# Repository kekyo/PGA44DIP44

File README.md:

# PGA44 to DIP44 socket PCB project

## What is this?

* This is very simple electric circuit diagram on EAGLE CAD.
* This is my first trial for learn how to use EAGLE CAD.
* I made for prototyping CPLD device (Xilinx XC95 series) on the breadboards.

## Artworks

* Xilinx XC9536/XC9572 version

* Side-by-side pure converter version

## How to use

### Xilinx XC9536/XC9572 version

TODO: More improving...

* You have to solder PGA44-PLCC44 socket and DIP22 x 2 headers.
* If your usage is side by side mapped pin conversion, you have to no additional works.
* If your usage is Xilinx XC95 series, add jumper pin header to head of board and solder x2 path-capacitors (ex: 0.1uF) onto SMD jumpers bottom of center board.
  * SMD jumpers shorts circuit between 21-41(VCCINT), 23-10-31(GND).
  * If jumper pin header closed, it shorts circuit between VCCINT and VCCIO. It means commonly voltage usage.

TODO: Example solder photos.

### Side-by-side pure converter version

* You have to solder PGA44-PLCC44 socket and DIP22 x 2 headers.
* Done!

TODO: Example solder photos.

## LICENSE

* [Under CC BY-NC-SA 4.0](https://creativecommons.org/licenses/by-nc-sa/4.0/)

## History

* 1.1
  * Fatal misassignement fixed for PGA44.
  * Split simple side-by-side pure converter version (see also pure-converter branch).
* 1.0
  * First public release.

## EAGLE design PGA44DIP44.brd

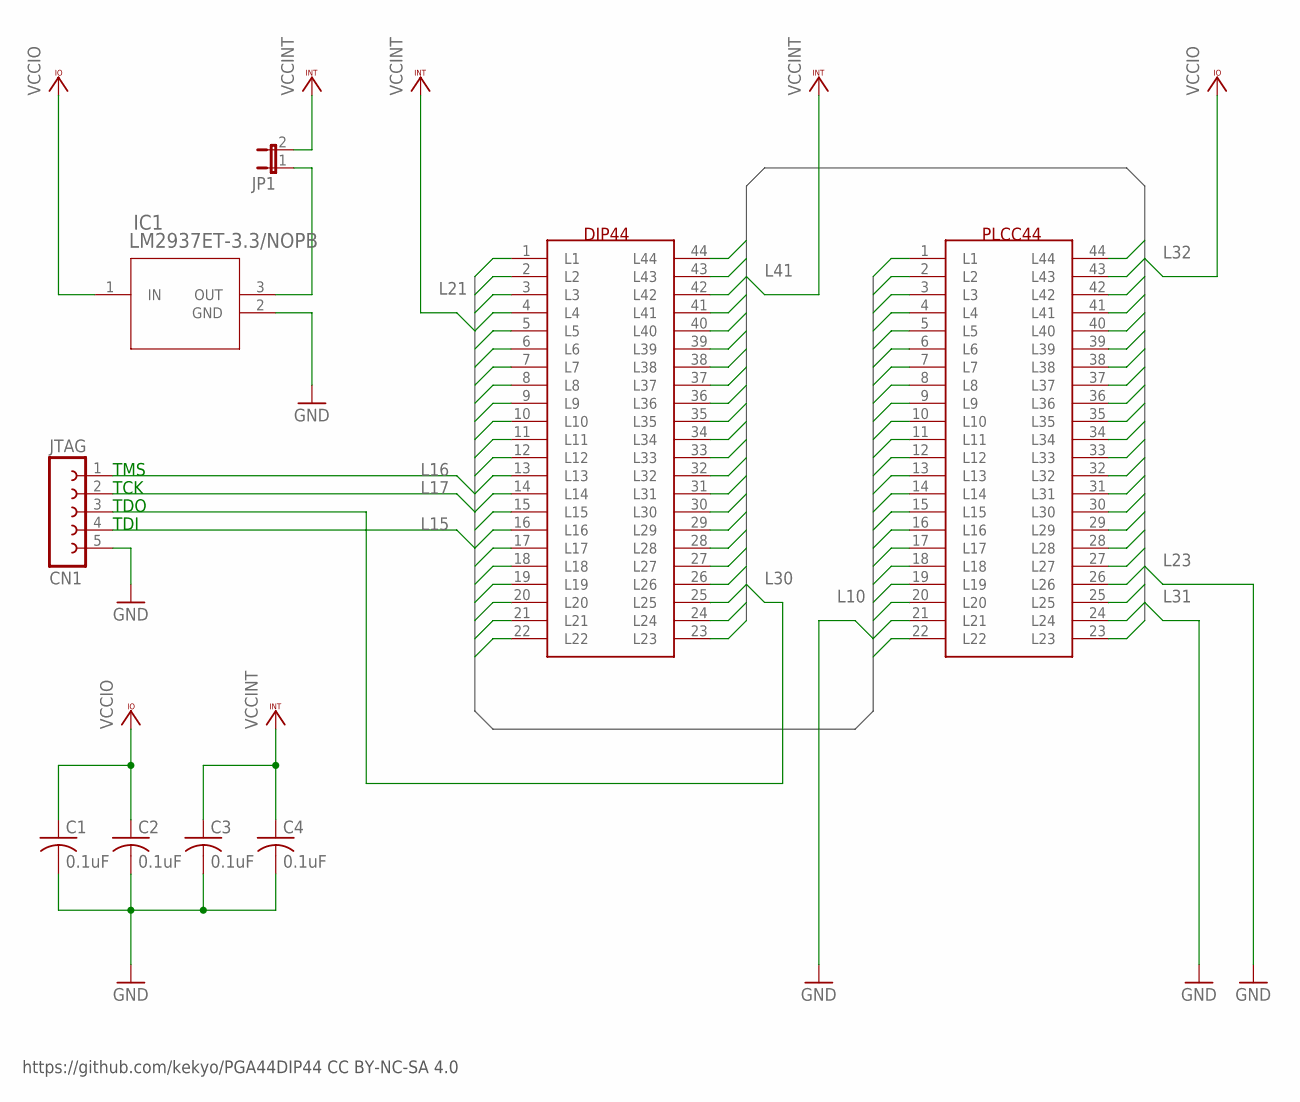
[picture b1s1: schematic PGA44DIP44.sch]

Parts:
C1, C2, C3, C4: 0.1uF; C050-024X044
CN1: JTAG; FE05-1
DIP44: DIP44
IC1: LM2937ET-3.3/NOPB; T03B
JP1: JP1E; JP1
PLCC44: PGA44

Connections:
GND: C1.2, C2.2, C3.2, C4.2, CN1.5, IC1.2 (GND)
L1: DIP44.1 (L1), PLCC44.1 (L1)
L2: DIP44.2 (L2), PLCC44.2 (L2)
L3: DIP44.3 (L3), PLCC44.3 (L3)
L4: DIP44.4 (L4), PLCC44.4 (L4)
L5: DIP44.5 (L5), PLCC44.5 (L5)
L6: DIP44.6 (L6), PLCC44.6 (L6)
L7: DIP44.7 (L7), PLCC44.7 (L7)
L8: DIP44.8 (L8), PLCC44.8 (L8)
L9: DIP44.9 (L9), PLCC44.9 (L9)
L10: DIP44.10 (L10), PLCC44.10 (L10)
L11: DIP44.11 (L11), PLCC44.11 (L11)
L12: DIP44.12 (L12), PLCC44.12 (L12)
L13: DIP44.13 (L13), PLCC44.13 (L13)
L14: DIP44.14 (L14), PLCC44.14 (L14)
L15: CN1.4, DIP44.15 (L15), PLCC44.15 (L15)
L16: CN1.1, DIP44.16 (L16), PLCC44.16 (L16)
L17: CN1.2, DIP44.17 (L17), PLCC44.17 (L17)
L18: DIP44.18 (L18), PLCC44.18 (L18)
L19: DIP44.19 (L19), PLCC44.19 (L19)
L20: DIP44.20 (L20), PLCC44.20 (L20)
L21: DIP44.21 (L21), PLCC44.21 (L21)
L22: DIP44.22 (L22), PLCC44.22 (L22)
L23: DIP44.23 (L23), PLCC44.23 (L23)
L24: DIP44.24 (L24), PLCC44.24 (L24)
L25: DIP44.25 (L25), PLCC44.25 (L25)
L26: DIP44.26 (L26), PLCC44.26 (L26)
L27: DIP44.27 (L27), PLCC44.27 (L27)
L28: DIP44.28 (L28), PLCC44.28 (L28)
L29: DIP44.29 (L29), PLCC44.29 (L29)
L30: CN1.3, DIP44.30 (L30), PLCC44.30 (L30)
L31: DIP44.31 (L31), PLCC44.31 (L31)
L32: DIP44.32 (L32), PLCC44.32 (L32)
L33: DIP44.33 (L33), PLCC44.33 (L33)
L34: DIP44.34 (L34), PLCC44.34 (L34)
L35: DIP44.35 (L35), PLCC44.35 (L35)
L36: DIP44.36 (L36), PLCC44.36 (L36)
L37: DIP44.37 (L37), PLCC44.37 (L37)
L38: DIP44.38 (L38), PLCC44.38 (L38)
L39: DIP44.39 (L39), PLCC44.39 (L39)
L40: DIP44.40 (L40), PLCC44.40 (L40)
L41: DIP44.41 (L41), PLCC44.41 (L41)
L42: DIP44.42 (L42), PLCC44.42 (L42)
L43: DIP44.43 (L43), PLCC44.43 (L43)
L44: DIP44.44 (L44), PLCC44.44 (L44)
unnamed: IC1.3 (OUT), JP1.1
VCCINT: C3.1, C4.1, JP1.2
VCCIO: C1.1, C2.1, IC1.1 (IN)

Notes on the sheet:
https://github.com/kekyo/PGA44DIP44 CC BY-NC-SA 4.0
TMS
TCK
TDO
TDI

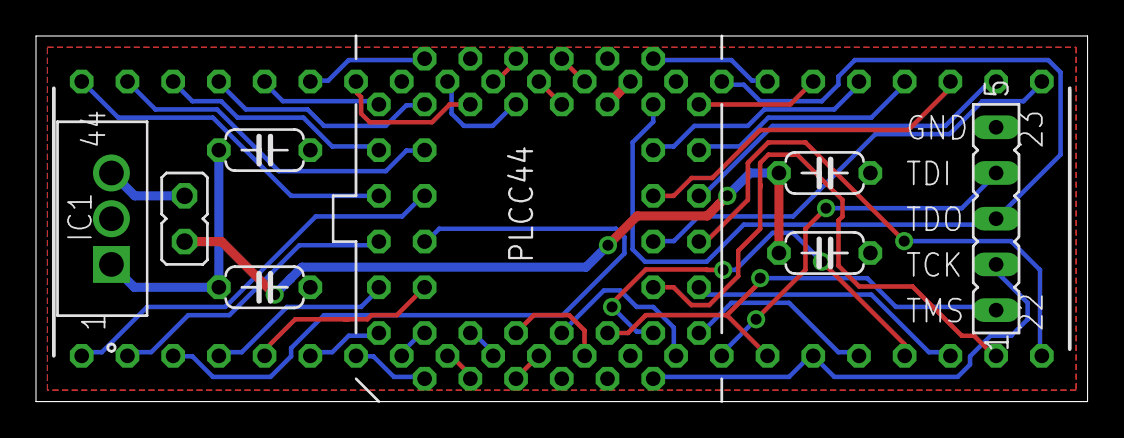
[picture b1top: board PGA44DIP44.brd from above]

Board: 2 copper layers, 58.4 x 20.3 mm, 9 parts (0 on the bottom side), 48 nets.

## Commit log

2017-03-27 Initial commit.
2017-03-27 Swap DIP side pins and try reroute.
2017-03-28 * Add smd jumper for XC95 usages. * Add jumper for XC95 commonly VCC usage. * Add gerber output.
2017-03-28 Add XC95 features.
2017-03-29 Move to origin.
2017-03-29 Adjust outer boxel.
2017-03-30 Fixed CC link.
2017-04-10 * Fatal misassignment fixed for PGA44. * Update to EAGLE 8.1.0
2017-04-10 Fixed artworks.
2017-04-10 Add gerver data.
2017-04-10 Gerber data move into sub directory.
2017-04-10 Artwork predesigning (WIP)
2017-04-14 Fixed XC9572 version.
2017-05-05 * Improve ground patterns. * Improve signal lines.
2017-05-05 Update images.
2017-05-05 Update readme.
2017-05-05 Update gerver data.
